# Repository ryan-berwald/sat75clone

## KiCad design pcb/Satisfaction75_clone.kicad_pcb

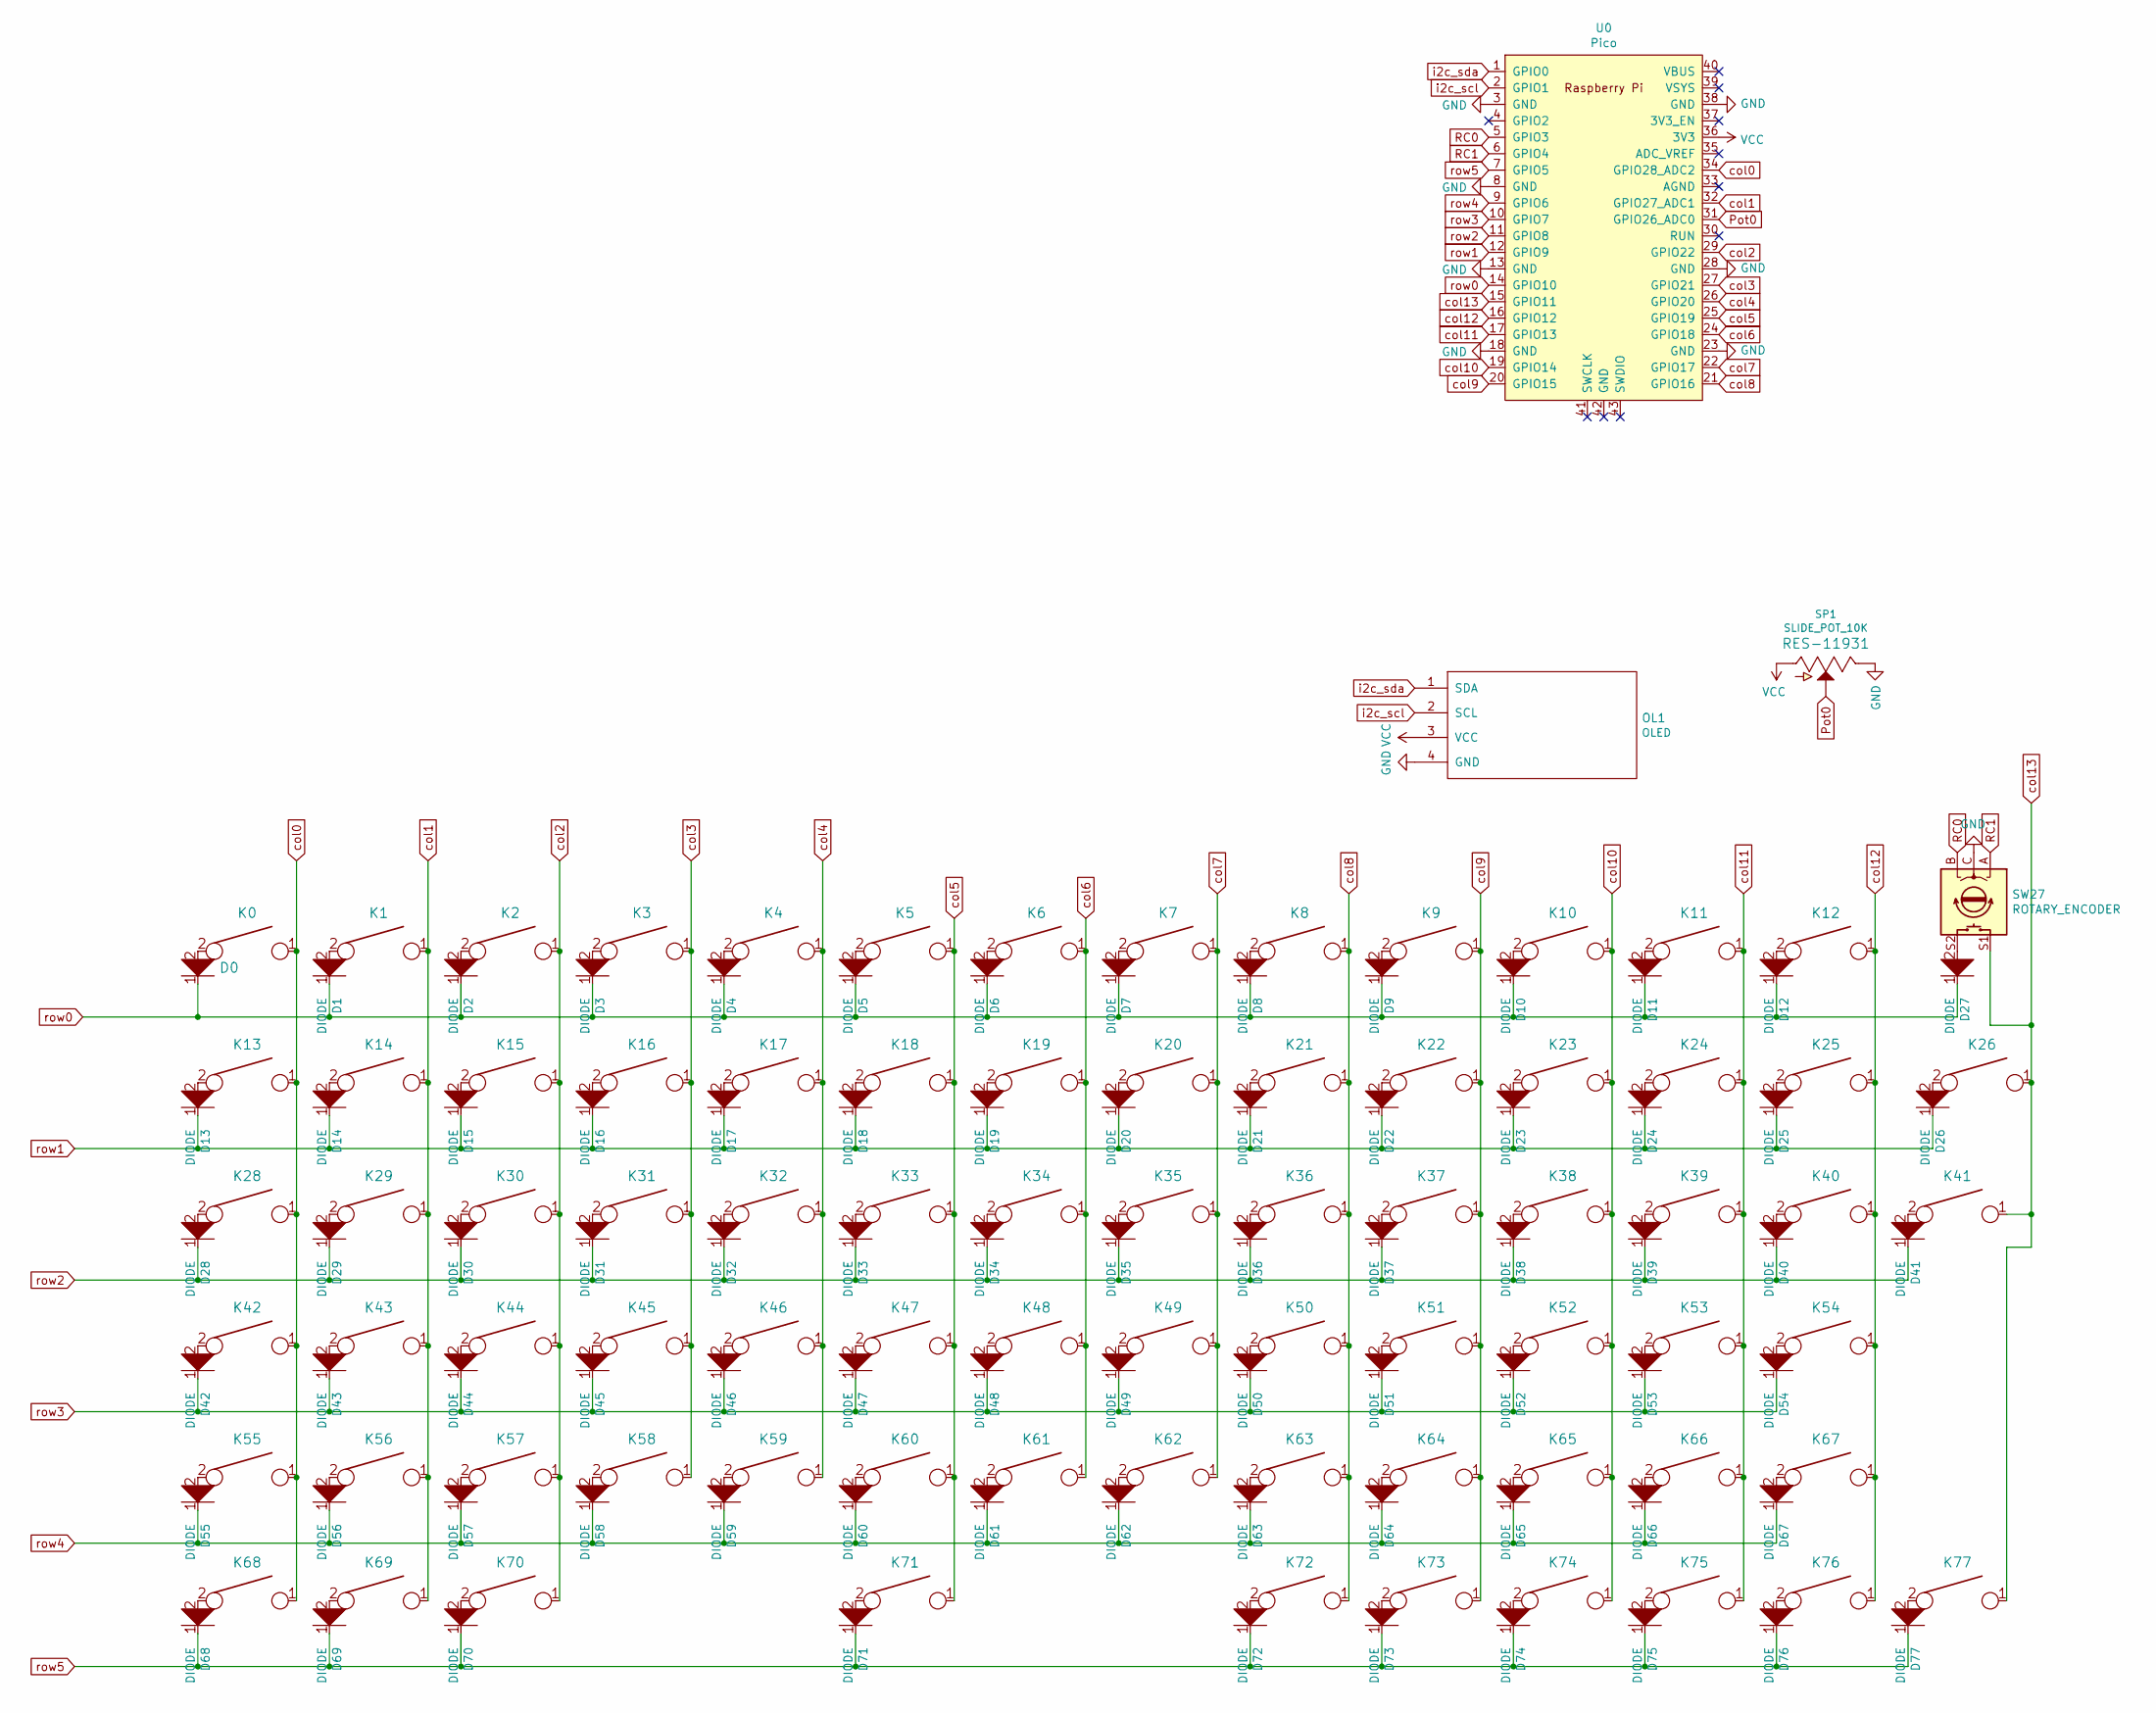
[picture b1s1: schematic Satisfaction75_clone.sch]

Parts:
D0: D; D_SOD123_axial
D1, D2, D3, D4, D5, D6, D7, D8, D9, D10, D11, D12, D13, D14, D15, D16, D17, D18, D19, D20, D21, D22, D23, D24, D25, D26, D27, D28, D29, D30, D31, D32, D33, D34, D35, D36, D37, D38, D39, D40, D41, D42, D43, D44, D45, D46, D47, D48, D49, D50, D51, D52, D53, D54, D55, D56, D57, D58, D59, D60, D61, D62, D63, D64, D65, D66, D67, D68, D69, D70, D71, D72, D73, D74, D75, D76, D77: DIODE; D_SOD123_axial
K0: Esc; Mx_Alps_100
K1: F1; Mx_Alps_100
K2: F2; Mx_Alps_100
K3: F3; Mx_Alps_100
K4: F4; Mx_Alps_100
K5: F5; Mx_Alps_100
K6: F6; Mx_Alps_100
K7: F7; Mx_Alps_100
K8: F8; Mx_Alps_100
K9: F9; Mx_Alps_100
K10: F10; Mx_Alps_100
K11: F11; Mx_Alps_100
K12: F12; Mx_Alps_100
K13: Mx_Alps_100
K14: 1; Mx_Alps_100
K15: 2; Mx_Alps_100
K16: 3; Mx_Alps_100
K17: 4; Mx_Alps_100
K18: 5; Mx_Alps_100
K19: 6; Mx_Alps_100
K20: 7; Mx_Alps_100
K21: 8; Mx_Alps_100
K22: 9; Mx_Alps_100
K23: 0; Mx_Alps_100
K24: -; Mx_Alps_100
K25: =; Mx_Alps_100
K26: BACK_SPC; Mx_Alps_200
K28: TAB; Mx_Alps_150
K29: Q; Mx_Alps_100
K30: W; Mx_Alps_100
K31: E; Mx_Alps_100
K32: R; Mx_Alps_100
K33: T; Mx_Alps_100
K34: Y; Mx_Alps_100
K35: U; Mx_Alps_100
K36: I; Mx_Alps_100
K37: O; Mx_Alps_100
K38: P; Mx_Alps_100
K39: [; Mx_Alps_100
K40: ]; Mx_Alps_100
K41: \\; Mx_Alps_150
K42: CAPS; Mx_Alps_175
K43: A; Mx_Alps_100
K44: S; Mx_Alps_100
K45: D; Mx_Alps_100
K46: F; Mx_Alps_100
K47: G; Mx_Alps_100
K48: H; Mx_Alps_100
K49: J; Mx_Alps_100
K50: K; Mx_Alps_100
K51: L; Mx_Alps_100
K52: ;; Mx_Alps_100
K53: '; Mx_Alps_100
K54: ENTER; Mx_Alps_225
K55: L_SHIFT; Mx_Alps_225
K56: Z; Mx_Alps_100
K57: X; Mx_Alps_100
K58: C; Mx_Alps_100
K59: V; Mx_Alps_100
K60: B; Mx_Alps_100
K61: N; Mx_Alps_100
K62: M; Mx_Alps_100
K63: ,; Mx_Alps_100
K64: .; Mx_Alps_100
K65: /; Mx_Alps_100
K66: R_SHIFT; Mx_Alps_175
K67: UP-ARROW; Mx_Alps_100
K68: L_CTRL; Mx_Alps_125
K69: META; Mx_Alps_125
K70: L_ALT; Mx_Alps_125
K71: SPACE; Mx_Alps_625
K72: R_ALT; Mx_Alps_100
K73: FN; Mx_Alps_100
K74: R_CTRL; Mx_Alps_100
K75: LEFT_ARROW; Mx_Alps_100
K76: DOWNARROW; Mx_Alps_100
K77: RIGHT ARROW; Mx_Alps_100
OL1: OLED; OLED_v2
SP1: SLIDE_POT_10K; SLIDER-MEDIUM
SW27: ROTARY_ENCODER; RotaryEncoder_EC11
U0: Pico; RPi_Pico_SMD_TH

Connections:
GND: OL1.4 (GND), SP1.TOP (E), SW27.C, U0.3 (GND), U0.8 (GND), U0.13 (GND), U0.18 (GND), U0.23 (GND), U0.28 (GND), U0.38 (GND)
unnamed: D0.2, K0.2
unnamed: D1.2, K1.2
unnamed: D2.2, K2.2
unnamed: D3.2, K3.2
unnamed: D4.2, K4.2
unnamed: D5.2, K5.2
unnamed: D6.2, K6.2
unnamed: D7.2, K7.2
unnamed: D8.2, K8.2
unnamed: D9.2, K9.2
unnamed: D10.2, K10.2
unnamed: D11.2, K11.2
unnamed: D12.2, K12.2
unnamed: D13.2, K13.2
unnamed: D14.2, K14.2
unnamed: D15.2, K15.2
unnamed: D16.2, K16.2
unnamed: D17.2, K17.2
unnamed: D18.2, K18.2
unnamed: D19.2, K19.2
unnamed: D20.2, K20.2
unnamed: D21.2, K21.2
unnamed: D22.2, K22.2
unnamed: D23.2, K23.2
unnamed: D24.2, K24.2
unnamed: D25.2, K25.2
unnamed: D26.2, K26.2
unnamed: D27.2, SW27.S2
unnamed: D28.2, K28.2
unnamed: D29.2, K29.2
unnamed: D30.2, K30.2
unnamed: D31.2, K31.2
unnamed: D32.2, K32.2
unnamed: D33.2, K33.2
unnamed: D34.2, K34.2
unnamed: D35.2, K35.2
unnamed: D36.2, K36.2
unnamed: D37.2, K37.2
unnamed: D38.2, K38.2
unnamed: D39.2, K39.2
unnamed: D40.2, K40.2
unnamed: D41.2, K41.2
unnamed: D42.2, K42.2
unnamed: D43.2, K43.2
unnamed: D44.2, K44.2
unnamed: D45.2, K45.2
unnamed: D46.2, K46.2
unnamed: D47.2, K47.2
unnamed: D48.2, K48.2
unnamed: D49.2, K49.2
unnamed: D50.2, K50.2
unnamed: D51.2, K51.2
unnamed: D52.2, K52.2
unnamed: D53.2, K53.2
unnamed: D54.2, K54.2
unnamed: D55.2, K55.2
unnamed: D56.2, K56.2
unnamed: D57.2, K57.2
unnamed: D58.2, K58.2
unnamed: D59.2, K59.2
unnamed: D60.2, K60.2
unnamed: D61.2, K61.2
unnamed: D62.2, K62.2
unnamed: D63.2, K63.2
unnamed: D64.2, K64.2
unnamed: D65.2, K65.2
unnamed: D66.2, K66.2
unnamed: D67.2, K67.2
unnamed: D68.2, K68.2
unnamed: D69.2, K69.2
unnamed: D70.2, K70.2
unnamed: D71.2, K71.2
unnamed: D72.2, K72.2
unnamed: D73.2, K73.2
unnamed: D74.2, K74.2
unnamed: D75.2, K75.2
unnamed: D76.2, K76.2
unnamed: D77.2, K77.2
Pot0: SP1.WIPE (S), U0.31 (GPIO26_ADC0)
RC0: SW27.B, U0.5 (GPIO3)
RC1: SW27.A, U0.6 (GPIO4)
VCC: OL1.3 (VCC), SP1.BOTT (A), U0.36 (3V3)
col0: K0.1, K13.1, K28.1, K42.1, K55.1, K68.1, U0.34 (GPIO28_ADC2)
col1: K1.1, K14.1, K29.1, K43.1, K56.1, K69.1, U0.32 (GPIO27_ADC1)
col2: K2.1, K15.1, K30.1, K44.1, K57.1, K70.1, U0.29 (GPIO22)
col3: K3.1, K16.1, K31.1, K45.1, K58.1, U0.27 (GPIO21)
col4: K4.1, K17.1, K32.1, K46.1, K59.1, U0.26 (GPIO20)
col5: K5.1, K18.1, K33.1, K47.1, K60.1, K71.1, U0.25 (GPIO19)
col6: K6.1, K19.1, K34.1, K48.1, K61.1, U0.24 (GPIO18)
col7: K7.1, K20.1, K35.1, K49.1, K62.1, U0.22 (GPIO17)
col8: K8.1, K21.1, K36.1, K50.1, K63.1, K72.1, U0.21 (GPIO16)
col9: K9.1, K22.1, K37.1, K51.1, K64.1, K73.1, U0.20 (GPIO15)
col10: K10.1, K23.1, K38.1, K52.1, K65.1, K74.1, U0.19 (GPIO14)
col11: K11.1, K24.1, K39.1, K53.1, K66.1, K75.1, U0.17 (GPIO13)
col12: K12.1, K25.1, K40.1, K54.1, K67.1, K76.1, U0.16 (GPIO12)
col13: K26.1, K41.1, K77.1, SW27.S1, U0.15 (GPIO11)
i2c_scl: OL1.2 (SCL), U0.2 (GPIO1)
i2c_sda: OL1.1 (SDA), U0.1 (GPIO0)
row0: D0.1, D1.1, D2.1, D3.1, D4.1, D5.1, D6.1, D7.1, D8.1, D9.1, D10.1, D11.1, D12.1, D27.1, U0.14 (GPIO10)
row1: D13.1, D14.1, D15.1, D16.1, D17.1, D18.1, D19.1, D20.1, D21.1, D22.1, D23.1, D24.1, D25.1, D26.1, U0.12 (GPIO9)
row2: D28.1, D29.1, D30.1, D31.1, D32.1, D33.1, D34.1, D35.1, D36.1, D37.1, D38.1, D39.1, D40.1, D41.1, U0.11 (GPIO8)
row3: D42.1, D43.1, D44.1, D45.1, D46.1, D47.1, D48.1, D49.1, D50.1, D51.1, D52.1, D53.1, D54.1, U0.10 (GPIO7)
row4: D55.1, D56.1, D57.1, D58.1, D59.1, D60.1, D61.1, D62.1, D63.1, D64.1, D65.1, D66.1, D67.1, U0.9 (GPIO6)
row5: D68.1, D69.1, D70.1, D71.1, D72.1, D73.1, D74.1, D75.1, D76.1, D77.1, U0.7 (GPIO5)

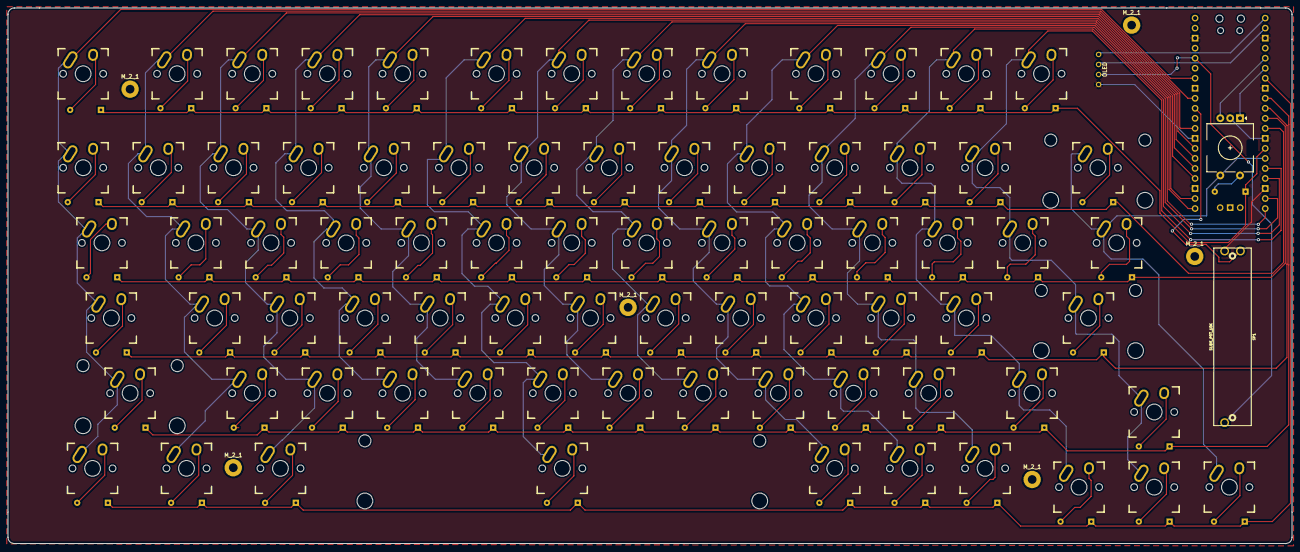
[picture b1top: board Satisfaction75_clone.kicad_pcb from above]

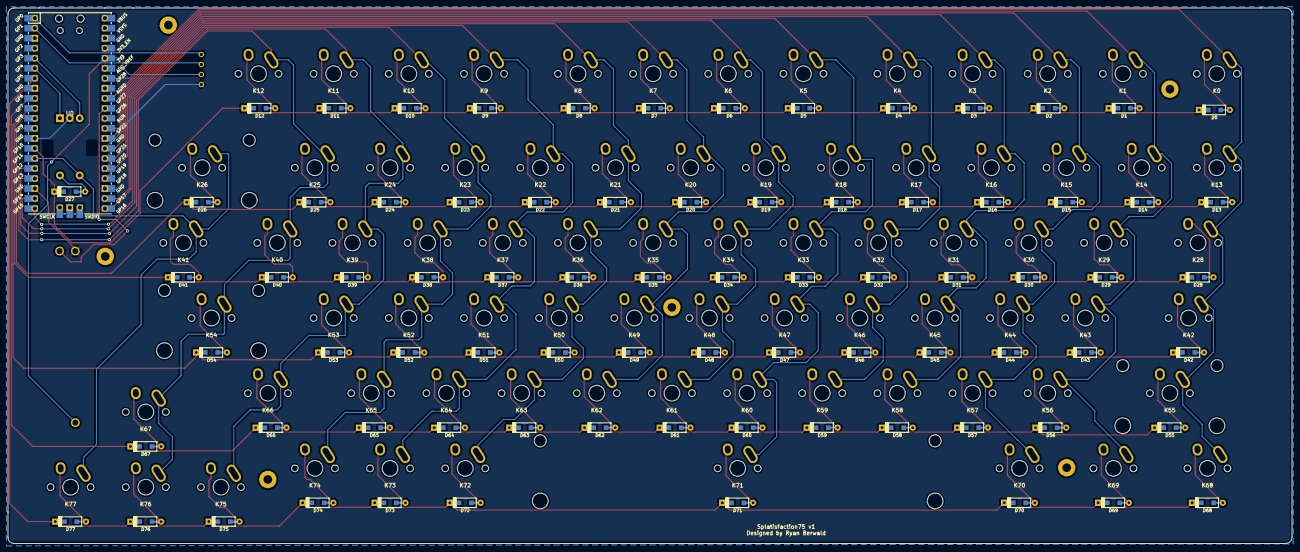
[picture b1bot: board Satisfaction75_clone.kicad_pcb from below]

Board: 2 copper layers, 325.4 x 135.7 mm, 165 parts (79 on the bottom side), 105 nets.

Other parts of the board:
M_2_1, M_2_1#2, M_2_1#3, M_2_1#4, M_2_1#5, M_2_1#6: MountingHole_2.2mm_M2_Pad

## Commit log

2023-11-11 Added case files
